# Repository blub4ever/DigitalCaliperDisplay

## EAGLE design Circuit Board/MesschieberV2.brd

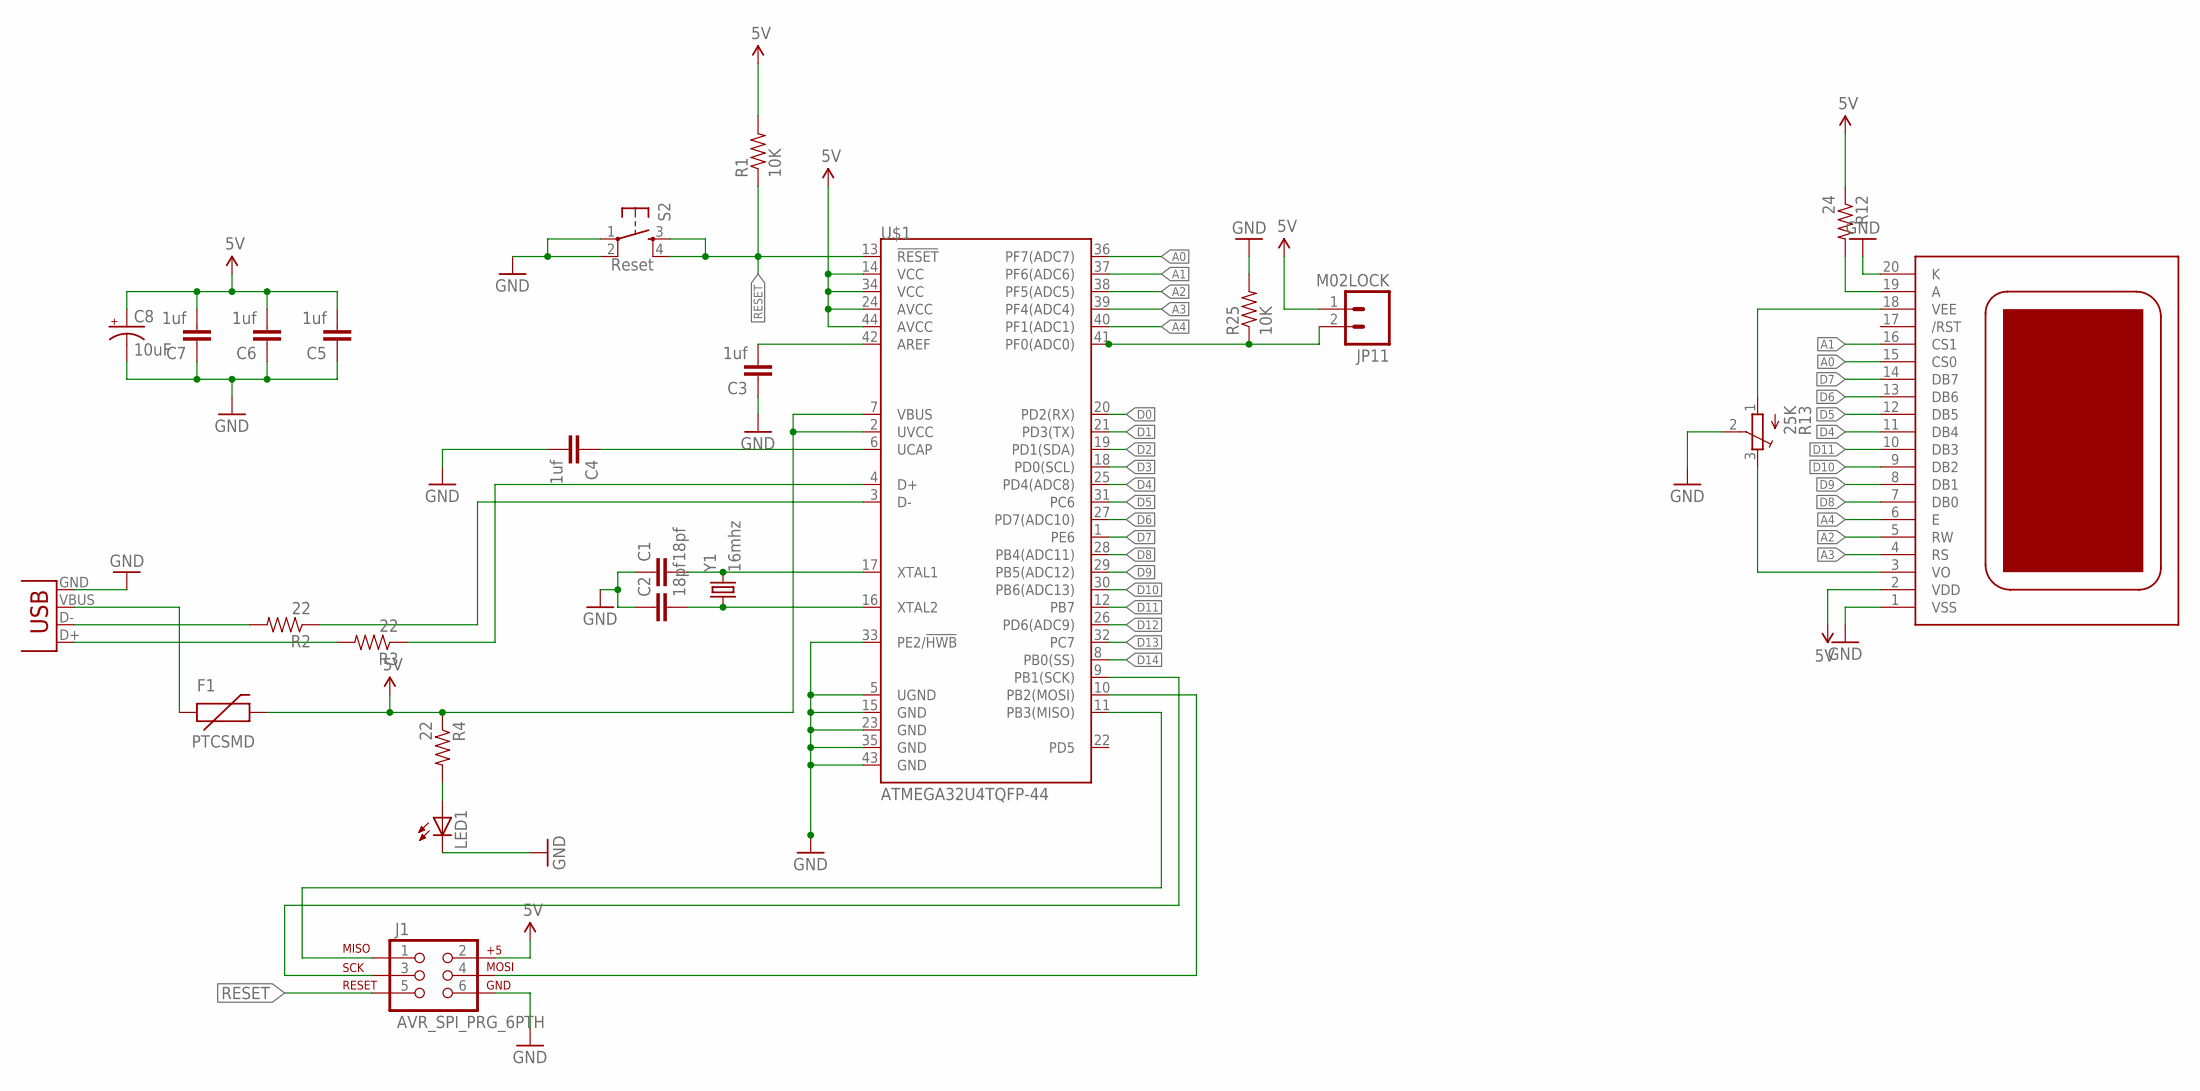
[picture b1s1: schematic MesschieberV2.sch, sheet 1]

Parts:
C1, C2: 18pf; 0805
C3, C4, C5, C6, C7: 1uf; 0805
C8: 10uF; EIA3528
F1: PTCSMD; PTC-1206
J1: AVR_SPI_PRG_6PTH; 2X3
JP7: USB-SMD-NS; USB-MINIB-NOSTOP
JP11: M02LOCK; 1X02_LOCK
LED1: LEDSML0805; SML0805
R1, R25: 10K; 0805
R2, R3, R4: 22; 0805
R12: 24; 0805
R13: 25K; SM-42/43A
S2: Reset; TACTILE_SWITCH_SMD
U$1: ATMEGA32U4TQFP-44; TQFP44
U$2: TS12864A; TS12864
Y1: 16mhz; CRYSTAL-SMD-5X3

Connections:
5V: C5.2, C6.2, C7.2, C8.A (+), F1.2, J1.2, JP11.1, R1.2, R4.1, R12.1, U$1.2 (UVCC), U$1.7 (VBUS), U$1.14 (VCC), U$1.24 (AVCC), U$1.34 (VCC), U$1.44 (AVCC), U$2.2 (VDD); also elsewhere on the board
A: R12.2, U$2.19 (A)
A0: U$1.36 (PF7(ADC7)), U$2.15 (CS0)
A1: U$1.37 (PF6(ADC6)), U$2.16 (CS1)
A2: U$1.38 (PF5(ADC5)), U$2.5 (RW)
A3: U$1.39 (PF4(ADC4)), U$2.4 (RS)
A4: U$1.40 (PF1(ADC1)), U$2.6 (E)
D0: U$1.20 (PD2(RX)); also elsewhere on the board
D1: U$1.21 (PD3(TX)); also elsewhere on the board
D2: U$1.19 (PD1(SDA)); also elsewhere on the board
D3: U$1.18 (PD0(SCL)); also elsewhere on the board
D4: U$1.25 (PD4(ADC8)), U$2.11 (DB4)
D5: U$1.31 (PC6), U$2.12 (DB5)
D6: U$1.27 (PD7(ADC10)), U$2.13 (DB6)
D7: U$1.1 (PE6), U$2.14 (DB7)
D8: U$1.28 (PB4(ADC11)), U$2.7 (DB0)
D9: U$1.29 (PB5(ADC12)), U$2.8 (DB1)
D10: U$1.30 (PB6(ADC13)), U$2.9 (DB2)
D11: U$1.12 (PB7), U$2.10 (DB3)
D12: U$1.26 (PD6(ADC9))
D13: U$1.32 (PC7); also elsewhere on the board
D14: U$1.8 (PB0(SS)); also elsewhere on the board
GND: C1.1, C2.1, C3.1, C4.2, C5.1, C6.1, C7.1, C8.C (-), J1.6, JP7.GND, LED1.C, R13.2 (S), R25.2, S2.1, S2.2, U$1.5 (UGND), U$1.15 (GND), U$1.23 (GND), U$1.33 (PE2/!HWB), U$1.35 (GND), U$1.43 (GND), U$2.1 (VSS), U$2.20 (K); also elsewhere on the board
unnamed: C3.2, U$1.42 (AREF)
unnamed: C2.2, U$1.16 (XTAL2), Y1.1
unnamed: C1.2, U$1.17 (XTAL1), Y1.3 (2)
unnamed: JP7.D-, R2.2
unnamed: JP7.D+, R3.2
unnamed: R3.1, U$1.4 (D+)
unnamed: R2.1, U$1.3 (D-)
unnamed: F1.1, JP7.VBUS
unnamed: LED1.A, R4.2
unnamed: J1.3, U$1.9 (PB1(SCK))
unnamed: J1.1, U$1.11 (PB3(MISO))
unnamed: J1.4, U$1.10 (PB2(MOSI))
unnamed: C4.1, U$1.6 (UCAP)
unnamed: JP11.2, R25.1, U$1.41 (PF0(ADC0))
unnamed: R13.3 (E), U$2.3 (VO)
RESET: J1.5, R1.1, S2.3, S2.4, U$1.13 (!RESET)
VEE: R13.1 (A), U$2.18 (VEE)

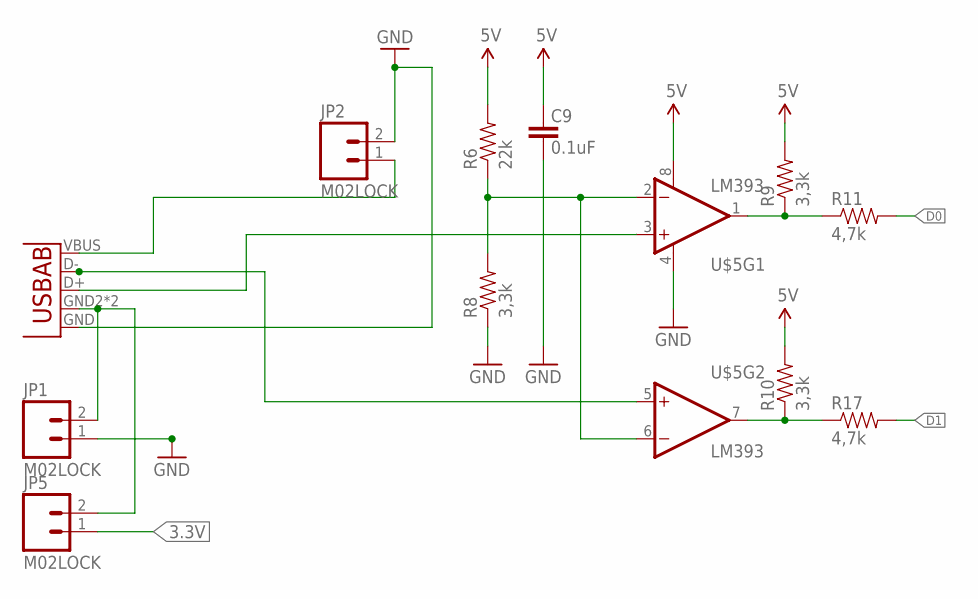
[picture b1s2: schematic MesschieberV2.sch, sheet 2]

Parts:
C9: 0.1uF; 0805
JP1, JP2, JP5: M02LOCK; 1X02_LOCK
R6: 22k; 0805
R8, R9, R10: 3,3k; 0805
R11, R17: 4,7k; 0805
U$5: LM393; SO08
U$7: USB-A

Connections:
3.3V: JP5.1; also elsewhere on the board
5V: C9.2, R6.2, R9.2, R10.2, U$5.8 (V+); also elsewhere on the board
D0: R11.2; also elsewhere on the board
D1: R17.2; also elsewhere on the board
DATA1: R9.1, R11.1, U$5.1 (OUT)
GND: C9.1, JP1.1, JP2.2, R8.1, U$5.4 (V-), U$7.GND; also elsewhere on the board
unnamed: R6.1, R8.2, U$5.2 (-IN), U$5.6 (-IN)
unnamed: U$5.3 (+IN), U$7.D+
unnamed: U$5.5 (+IN), U$7.D-
unnamed: JP2.1, U$7.VBUS
unnamed: JP1.2, JP5.2, U$7.GND2 (USBID), U$7.GND3 (USBID)
SCK1: R10.1, R17.1, U$5.7 (OUT)

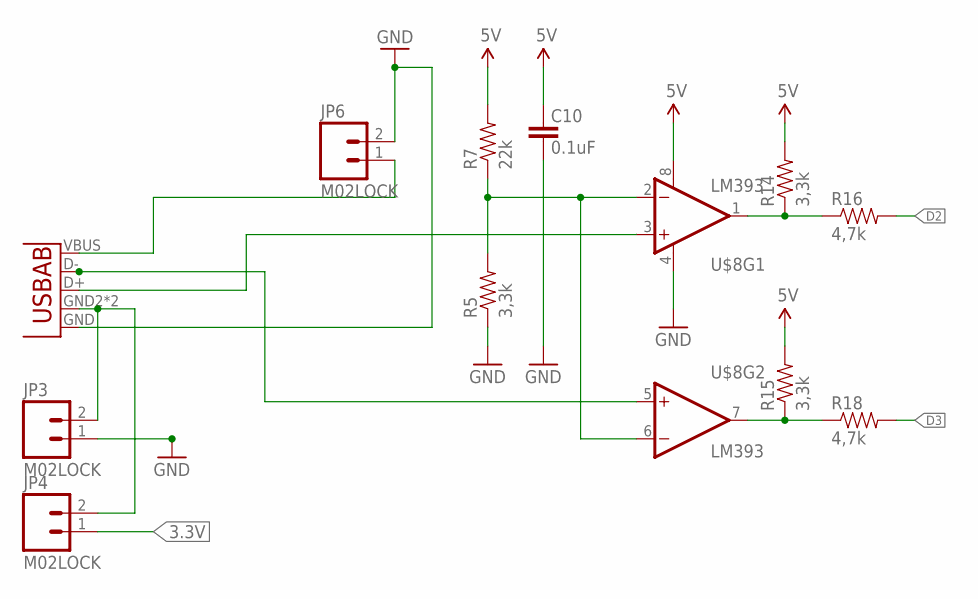
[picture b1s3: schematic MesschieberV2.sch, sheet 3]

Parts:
C10: 0.1uF; 0805
JP3, JP4, JP6: M02LOCK; 1X02_LOCK
R5, R14, R15: 3,3k; 0805
R7: 22k; 0805
R16, R18: 4,7k; 0805
U$8: LM393; SO08
U$9: USB-A

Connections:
3.3V: JP4.1; also elsewhere on the board
5V: C10.2, R7.2, R14.2, R15.2, U$8.8 (V+); also elsewhere on the board
D2: R16.2; also elsewhere on the board
D3: R18.2; also elsewhere on the board
DATA2: R14.1, R16.1, U$8.1 (OUT)
GND: C10.1, JP3.1, JP6.2, R5.1, U$8.4 (V-), U$9.GND; also elsewhere on the board
unnamed: R5.2, R7.1, U$8.2 (-IN), U$8.6 (-IN)
unnamed: U$8.3 (+IN), U$9.D+
unnamed: U$8.5 (+IN), U$9.D-
unnamed: JP6.1, U$9.VBUS
unnamed: JP3.2, JP4.2, U$9.GND2 (USBID), U$9.GND3 (USBID)
SCK2: R15.1, R18.1, U$8.7 (OUT)

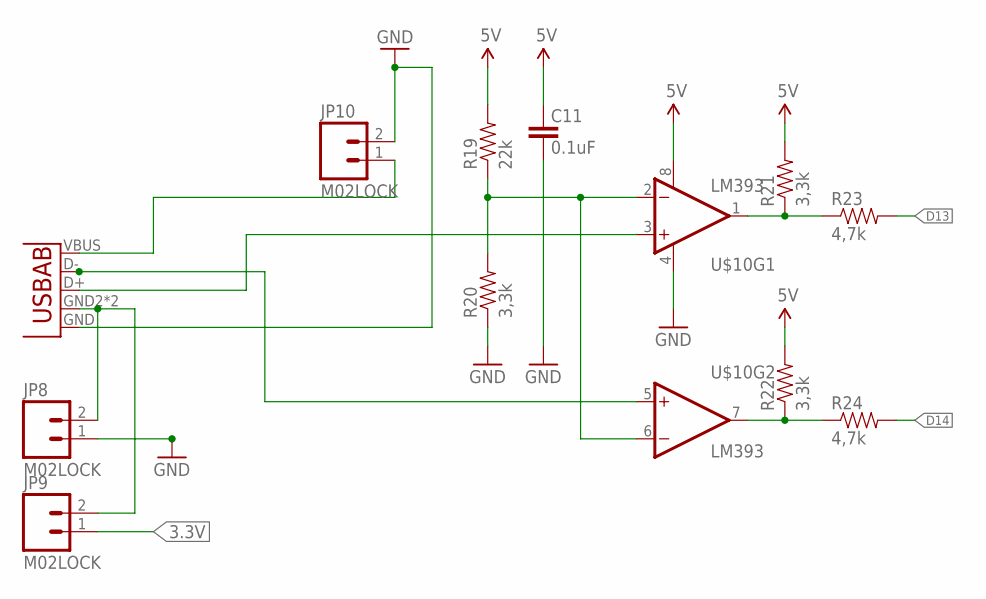
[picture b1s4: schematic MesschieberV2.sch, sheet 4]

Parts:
C11: 0.1uF; 0805
JP8, JP9, JP10: M02LOCK; 1X02_LOCK
R19: 22k; 0805
R20, R21, R22: 3,3k; 0805
R23, R24: 4,7k; 0805
U$10: LM393; SO08
U$11: USB-A

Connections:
3.3V: JP9.1; also elsewhere on the board
5V: C11.2, R19.2, R21.2, R22.2, U$10.8 (V+); also elsewhere on the board
D13: R23.2; also elsewhere on the board
D14: R24.2; also elsewhere on the board
DATA3: R21.1, R23.1, U$10.1 (OUT)
GND: C11.1, JP8.1, JP10.2, R20.1, U$10.4 (V-), U$11.GND; also elsewhere on the board
unnamed: R19.1, R20.2, U$10.2 (-IN), U$10.6 (-IN)
unnamed: U$10.3 (+IN), U$11.D+
unnamed: U$10.5 (+IN), U$11.D-
unnamed: JP10.1, U$11.VBUS
unnamed: JP8.2, JP9.2, U$11.GND2 (USBID), U$11.GND3 (USBID)
SCK3: R22.1, R24.1, U$10.7 (OUT)

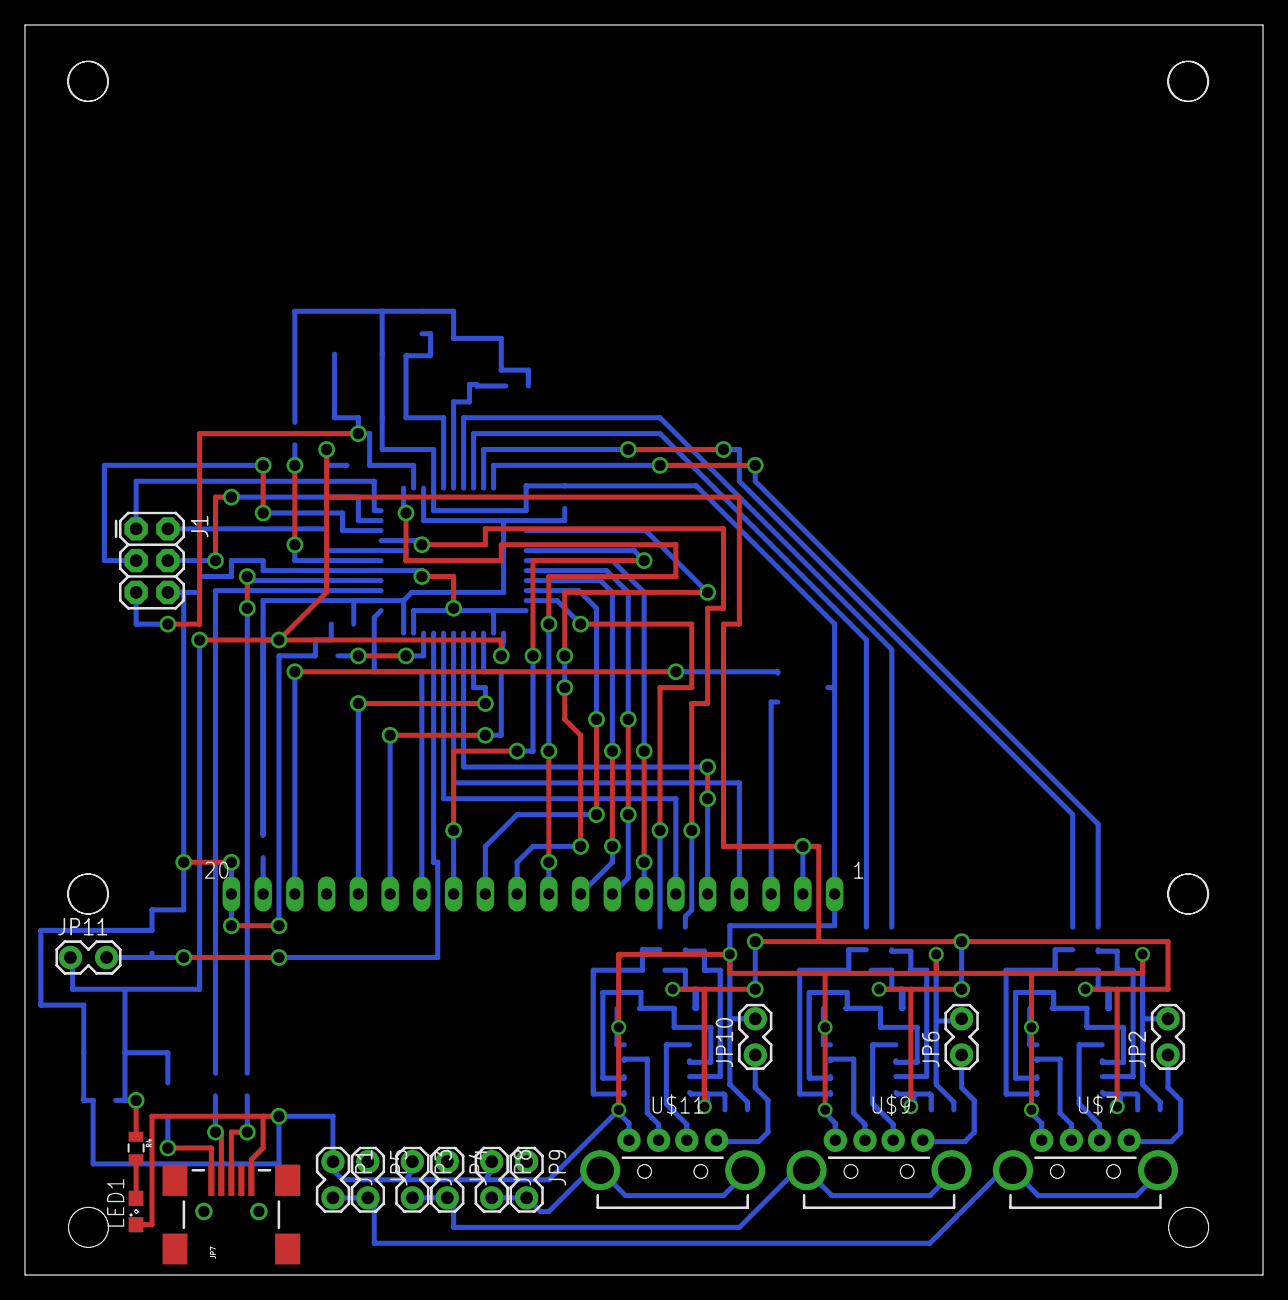
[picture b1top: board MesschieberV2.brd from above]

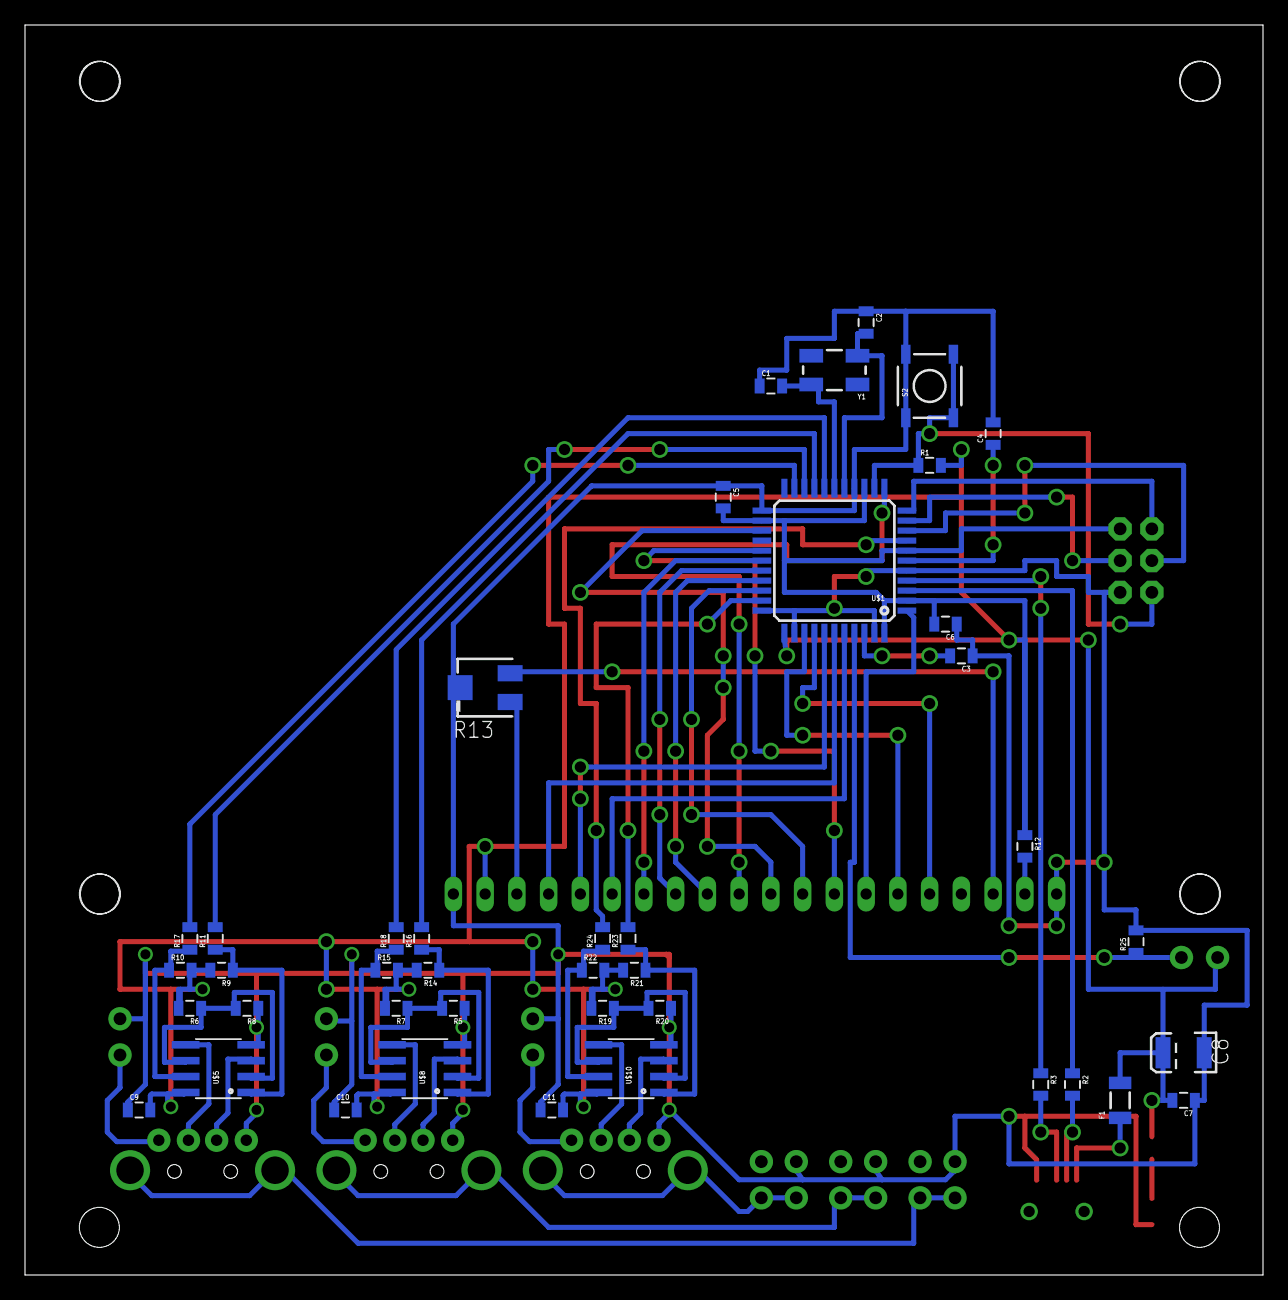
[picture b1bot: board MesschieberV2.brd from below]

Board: 2 copper layers, 99.0 x 100.0 mm, 60 parts (42 on the bottom side), 61 nets.

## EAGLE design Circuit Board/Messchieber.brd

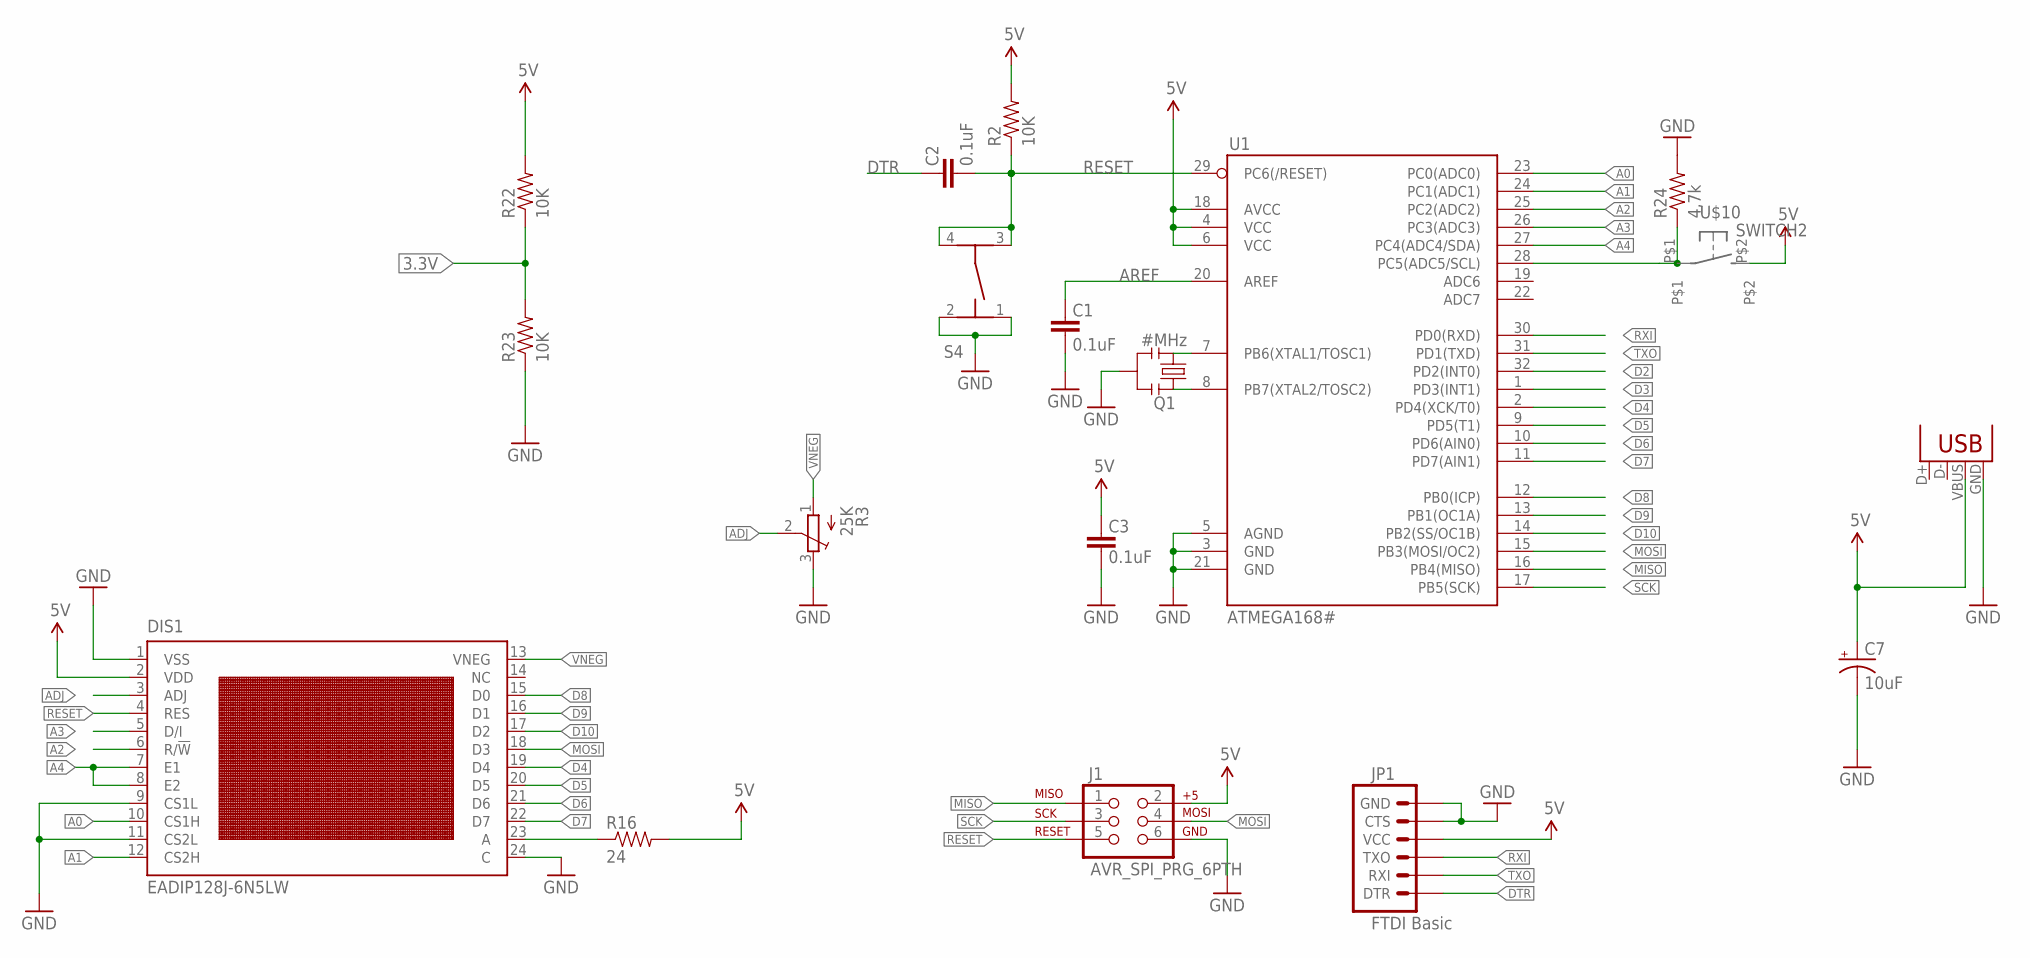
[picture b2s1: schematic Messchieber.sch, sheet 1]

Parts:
C1, C2, C3: 0.1uF; 0805
C7: 10uF; EIA3216
DIS1: EADIP128J-6N5LW; LCD-DIP128-64
J1: AVR_SPI_PRG_6PTH; 2X3
JP1: FTDI Basic; 1X06
JP7: USB-SMD-NS; USB-MINIB-NOSTOP
Q1: #MHz; RESONATOR-SMD
R2, R22, R23: 10K; 0805
R3: 25K; SM-42/43A
R16: 24; 0805
R24: 4,7k; 0805
S4: TASTER-9314_SMD
U1: ATMEGA168#; TQFP32-08
U$10: SWITCH2

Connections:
3.3V: R22.1, R23.2; also elsewhere on the board
5V: C3.2, C7.A (+), DIS1.2 (VDD), J1.2, JP1.4 (VCC), JP7.VBUS, R2.2, R16.2, R22.2, U1.4 (VCC), U1.6 (VCC), U1.18 (AVCC), U$10.P$2; also elsewhere on the board
A0: DIS1.10 (CS1H), U1.23 (PC0(ADC0))
A1: DIS1.12 (CS2H), U1.24 (PC1(ADC1))
A2: DIS1.6 (R/!W), U1.25 (PC2(ADC2))
A3: DIS1.5 (D/I), U1.26 (PC3(ADC3))
A4: DIS1.7 (E1), DIS1.8 (E2), U1.27 (PC4(ADC4/SDA))
ADJ: DIS1.3 (ADJ), R3.2 (S)
AREF: C1.2, U1.20 (AREF)
D2: U1.32 (PD2(INT0)); also elsewhere on the board
D3: U1.1 (PD3(INT1)); also elsewhere on the board
D4: DIS1.19 (D4), U1.2 (PD4(XCK/T0))
D5: DIS1.20 (D5), U1.9 (PD5(T1))
D6: DIS1.21 (D6), U1.10 (PD6(AIN0))
D7: DIS1.22 (D7), U1.11 (PD7(AIN1))
D8: DIS1.15 (D0), U1.12 (PB0(ICP))
D9: DIS1.16 (D1), U1.13 (PB1(OC1A))
D10: DIS1.17 (D2), U1.14 (PB2(SS/OC1B))
DTR: C2.2, JP1.1 (DTR)
GND: C1.1, C3.1, C7.C (-), DIS1.1 (VSS), DIS1.9 (CS1L), DIS1.11 (CS2L), DIS1.24 (C), J1.6, JP1.5 (CTS), JP1.6 (GND), JP7.GND, Q1.2, R3.3 (E), R23.1, R24.2, S4.1, S4.2, U1.3 (GND), U1.5 (AGND), U1.21 (GND); also elsewhere on the board
MISO: J1.1, U1.16 (PB4(MISO)); also elsewhere on the board
MOSI: DIS1.18 (D3), J1.4, U1.15 (PB3(MOSI/OC2))
unnamed: Q1.1, U1.8 (PB7(XTAL2/TOSC2))
unnamed: Q1.3, U1.7 (PB6(XTAL1/TOSC1))
unnamed: R24.1, U1.28 (PC5(ADC5/SCL)), U$10.P$1
unnamed: DIS1.23 (A), R16.1
RESET: C2.1, DIS1.4 (RES), J1.5, R2.1, S4.3, S4.4, U1.29 (PC6(/RESET))
RXI: JP1.3 (TXO), U1.30 (PD0(RXD)); also elsewhere on the board
SCK: J1.3, U1.17 (PB5(SCK)); also elsewhere on the board
TXO: JP1.2 (RXI), U1.31 (PD1(TXD)); also elsewhere on the board
VNEG: DIS1.13 (VNEG), R3.1 (A)

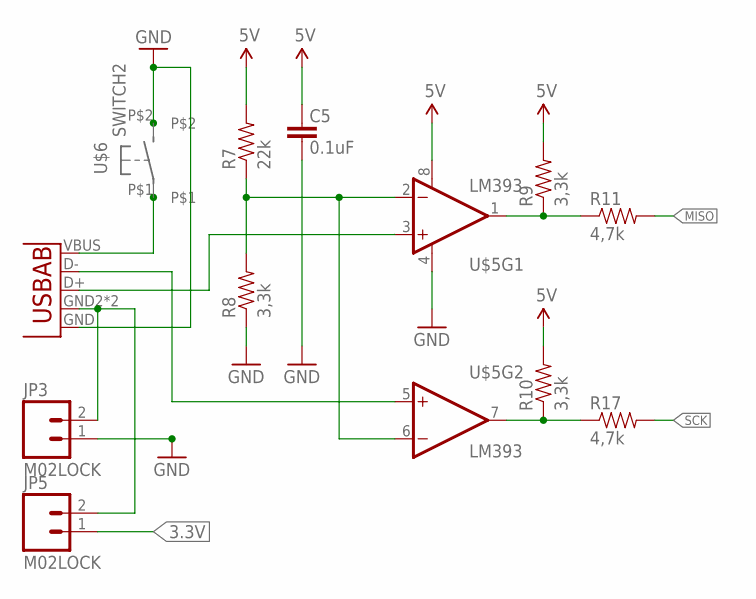
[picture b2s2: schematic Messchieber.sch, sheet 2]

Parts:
C5: 0.1uF; 0805
JP3, JP5: M02LOCK; 1X02_LOCK
R7: 22k; 0805
R8, R9, R10: 3,3k; 0805
R11, R17: 4,7k; 0805
U$5: LM393; SO08
U$6: SWITCH2
U$7: USB-A

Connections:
3.3V: JP5.1; also elsewhere on the board
5V: C5.2, R7.2, R9.2, R10.2, U$5.8 (V+); also elsewhere on the board
DATA1: R9.1, R11.1, U$5.1 (OUT)
GND: C5.1, JP3.1, R8.1, U$5.4 (V-), U$6.P$2, U$7.GND; also elsewhere on the board
MISO: R11.2; also elsewhere on the board
unnamed: R7.1, R8.2, U$5.2 (-IN), U$5.6 (-IN)
unnamed: U$5.3 (+IN), U$7.D+
unnamed: U$5.5 (+IN), U$7.D-
unnamed: U$6.P$1, U$7.VBUS
unnamed: JP3.2, JP5.2, U$7.GND2 (USBID), U$7.GND3 (USBID)
SCK: R17.2; also elsewhere on the board
SCK1: R10.1, R17.1, U$5.7 (OUT)

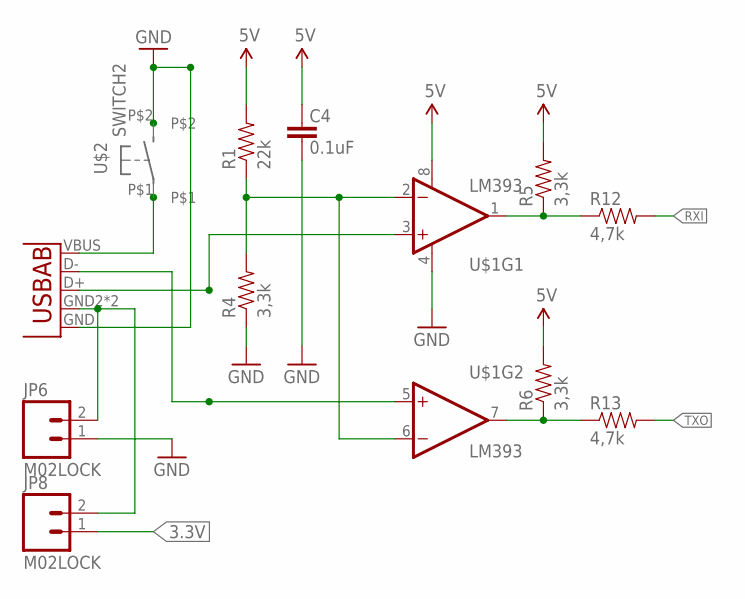
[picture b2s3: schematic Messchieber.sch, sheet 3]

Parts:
C4: 0.1uF; 0805
JP6, JP8: M02LOCK; 1X02_LOCK
R1: 22k; 0805
R4, R5, R6: 3,3k; 0805
R12, R13: 4,7k; 0805
U$1: LM393; SO08
U$2: SWITCH2
U$8: USB-A

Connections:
3.3V: JP8.1; also elsewhere on the board
5V: C4.2, R1.2, R5.2, R6.2, U$1.8 (V+); also elsewhere on the board
DATA2: R5.1, R12.1, U$1.1 (OUT)
GND: C4.1, JP6.1, R4.1, U$1.4 (V-), U$2.P$2, U$8.GND; also elsewhere on the board
unnamed: R1.1, R4.2, U$1.2 (-IN), U$1.6 (-IN)
unnamed: U$1.3 (+IN), U$8.D+
unnamed: U$1.5 (+IN), U$8.D-
unnamed: U$2.P$1, U$8.VBUS
unnamed: JP6.2, JP8.2, U$8.GND2 (USBID), U$8.GND3 (USBID)
RXI: R12.2; also elsewhere on the board
SCK2: R6.1, R13.1, U$1.7 (OUT)
TXO: R13.2; also elsewhere on the board

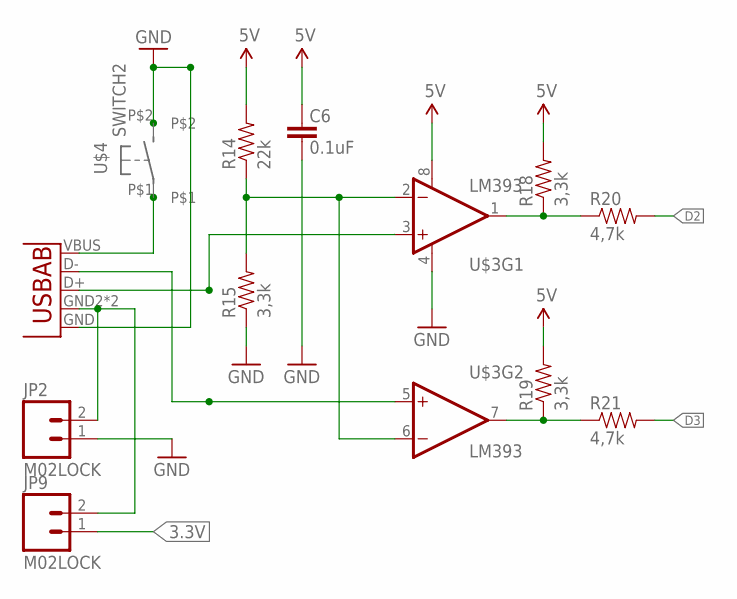
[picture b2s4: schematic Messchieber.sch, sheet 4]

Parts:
C6: 0.1uF; 0805
JP2, JP9: M02LOCK; 1X02_LOCK
R14: 22k; 0805
R15, R18, R19: 3,3k; 0805
R20, R21: 4,7k; 0805
U$3: LM393; SO08
U$4: SWITCH2
U$9: USB-A

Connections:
3.3V: JP9.1; also elsewhere on the board
5V: C6.2, R14.2, R18.2, R19.2, U$3.8 (V+); also elsewhere on the board
D2: R20.2; also elsewhere on the board
D3: R21.2; also elsewhere on the board
DATA3: R18.1, R20.1, U$3.1 (OUT)
GND: C6.1, JP2.1, R15.1, U$3.4 (V-), U$4.P$2, U$9.GND; also elsewhere on the board
unnamed: R14.1, R15.2, U$3.2 (-IN), U$3.6 (-IN)
unnamed: U$3.3 (+IN), U$9.D+
unnamed: U$3.5 (+IN), U$9.D-
unnamed: U$4.P$1, U$9.VBUS
unnamed: JP2.2, JP9.2, U$9.GND2 (USBID), U$9.GND3 (USBID)
SCK3: R19.1, R21.1, U$3.7 (OUT)

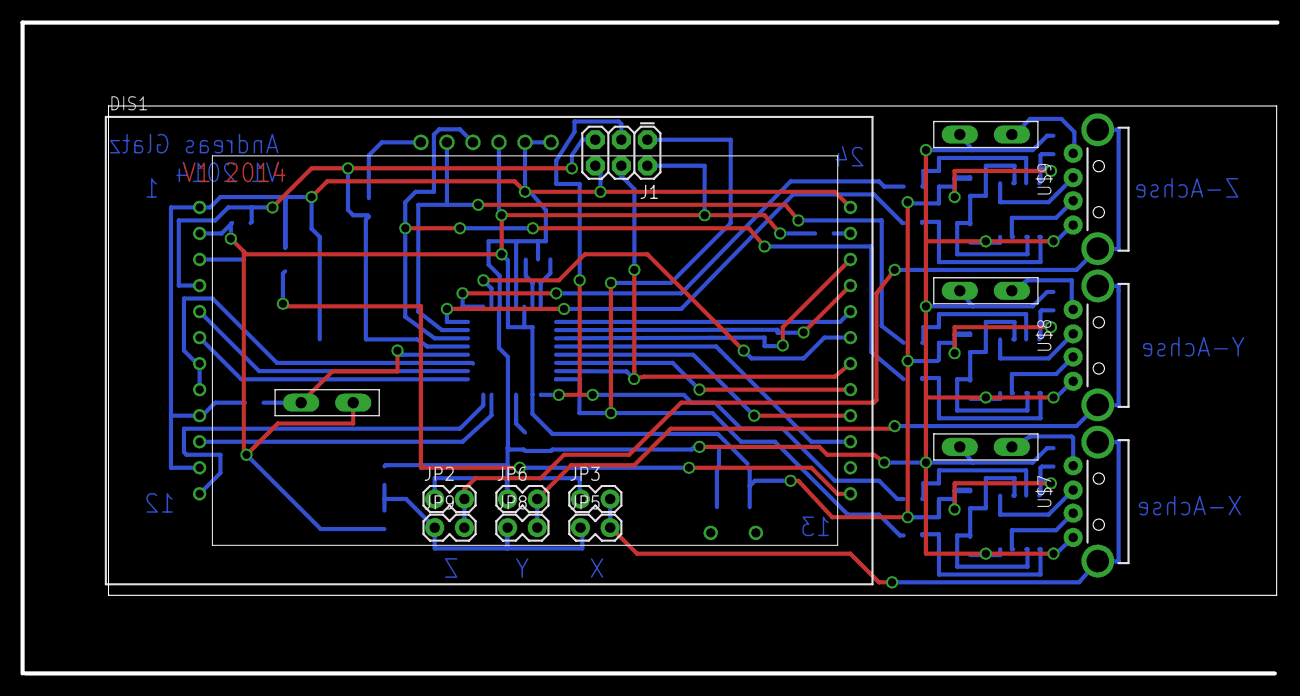
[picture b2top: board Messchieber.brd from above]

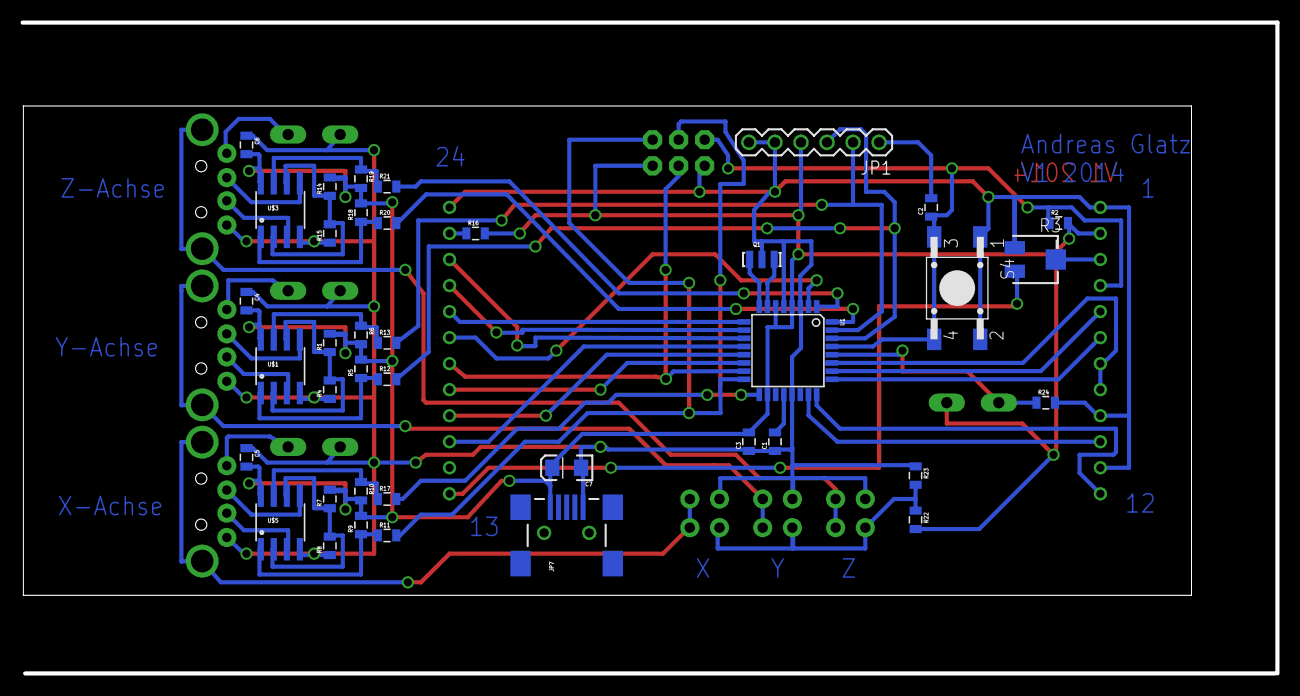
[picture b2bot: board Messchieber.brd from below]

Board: 2 copper layers, 122.4 x 63.5 mm, 54 parts (39 on the bottom side), 52 nets.

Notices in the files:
parts and their libraries:
SparkFun-Connectors: Licensing: Creative Commons ShareAlike 4.0 International - https://creativecommons.org/licenses/by-sa/4.0
